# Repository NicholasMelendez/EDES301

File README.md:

# EDES301
Repository for EDES301 course work

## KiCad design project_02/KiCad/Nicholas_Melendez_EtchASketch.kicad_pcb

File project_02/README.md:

# EDES301 Project_02: EtchASketch PCB Design

For my Second project in EDES301, I decided to design an Etch A Sketch PCB using KiCad. I was responsible for the KiCad Symbol and Footprint libraries, the KiCad Schematic, and the KiCad PCB layout. 

The EtchASketch was designed using the PocketBeagle Microprocessor, and it contains the following components:

* One Adafruit 2.8" TFT LCD with Touchscreen Breakout Board w/MicroSD Socket ( to Display EtchASketch Art)

* Two potentiometers ( To operate and draw using the EtchASketch)

* Three LEDs (Red, Green, and Blue for user color indication)

* Two Button (To swap colors and to reset the screen)

* One USB port (For future expansion)

* An Image of the GOAT Gojo Satoru

In addition to the KiCad files, the directory for project_02 also contains generated Gerber and Drill files for the PCB, A generated Bill of Materials document, Images of the Top and Bottom views of the PCB, a PDF of the Schematic, and a presentation containing the mechanical block diagram and the system block diagram

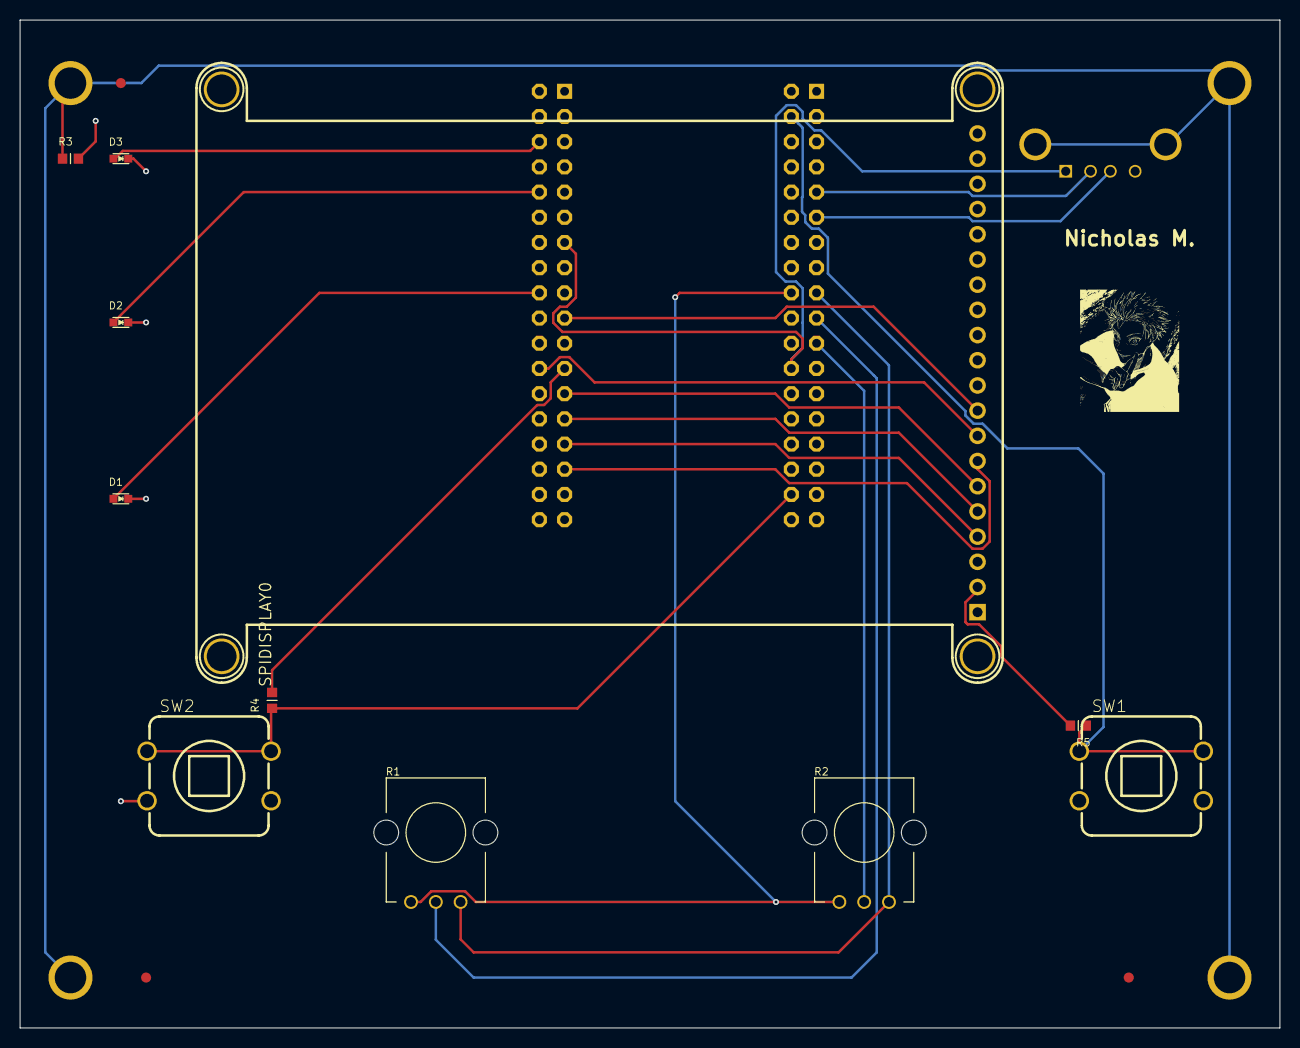
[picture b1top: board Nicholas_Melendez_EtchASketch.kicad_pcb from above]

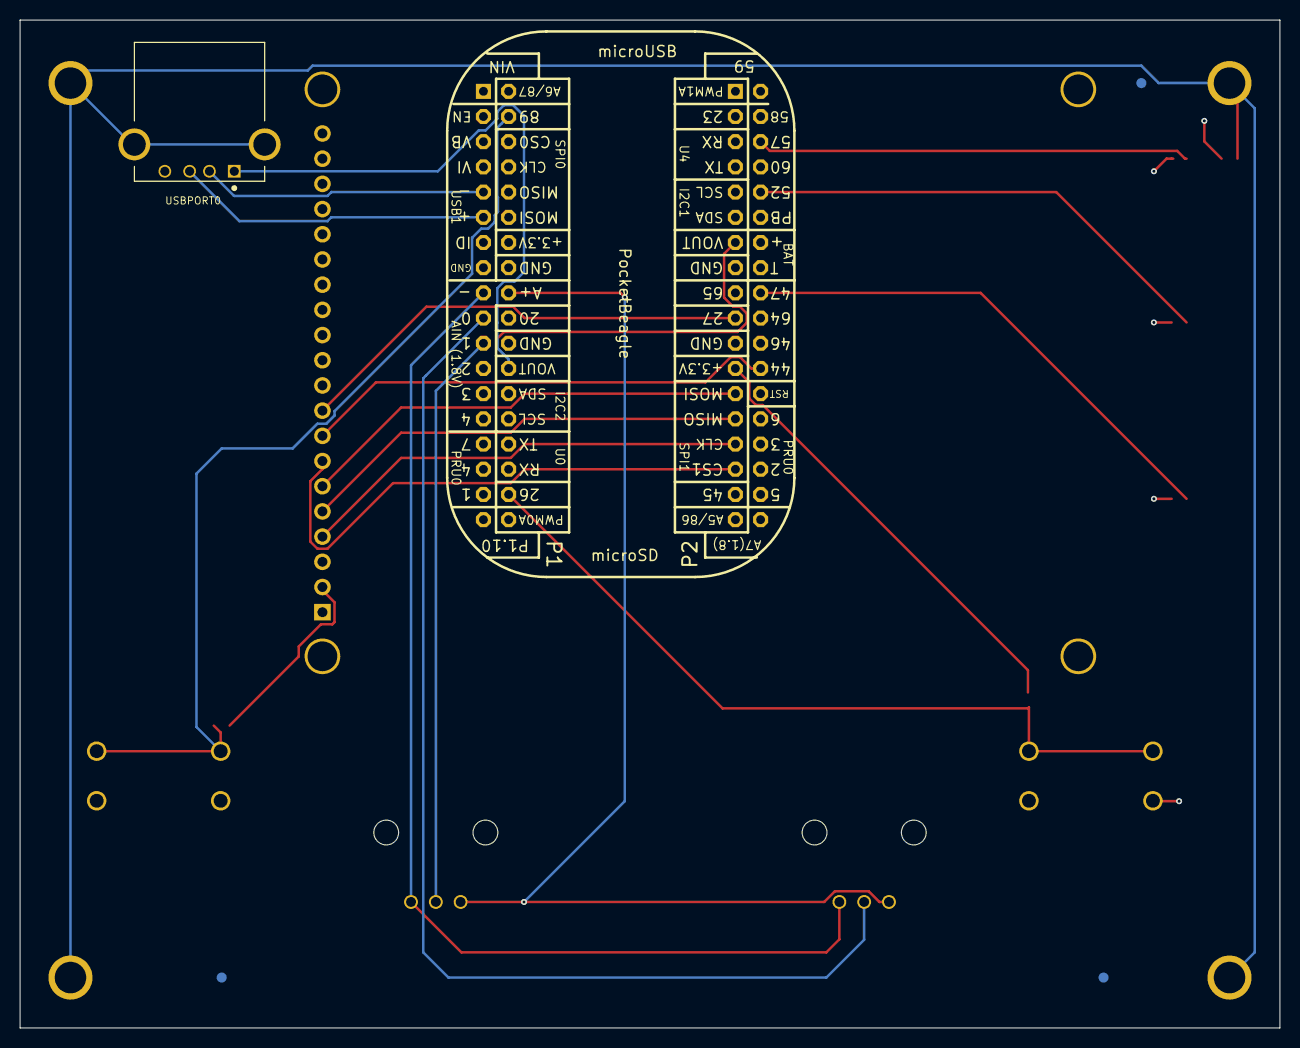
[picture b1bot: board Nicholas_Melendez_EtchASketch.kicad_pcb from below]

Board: 4 copper layers, 127.0 x 101.6 mm, 24 parts (5 on the bottom side), 21 nets.

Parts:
D1: BLUE_LED; EIA-STD
D2: GREEN_LED; EIA-STD
D3: RED_LED; EIA-STD
FUD1, FUD2, FUD3, FUD4, FUD5, FUD6: FIDUCIAL; FIDUCIAL_40MIL
MGT1, MGT2, MGT3, MGT4: MOUNTING_HOLE
Nicholas M.: LOGO; Nicholas_Melendez_GOJO
R1, R2: POTENTIOMETER; POT-PO90S
R3, R4, R5: 1k; R0603
SPIDISPLAY0: SCREEN
SW1, SW2: PUSH_BUTTON; BUTTON_12.5MM
U1: POCKETBEAGLE
USBPORT0: 292303-1; TE_292303-1

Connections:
ANALOG_GND: R1.CW, R2.CW, U1.P1_17
BLUE_LED: D1.ANODE, U1.P2_18
BUTTON_1: R5.1, SW1.1, SW1.3, U1.P1_04
BUTTON_2: R4.1, SW2.1, SW2.3, U1.P1_34
CGND: MGT1.P$1, MGT2.P$1, MGT3.P$1, MGT4.P$1, R3.1, USBPORT0.SH1, USBPORT0.SH2
CLK: SPIDISPLAY0.CLK, U1.P2_29
CS: SPIDISPLAY0.CS, U1.P2_31
DC: SPIDISPLAY0.DC, U1.P2_24
DM: U1.P1_09, USBPORT0.2
DP: U1.P1_11, USBPORT0.3
GND: D1.CATHODE, D2.CATHODE, D3.CATHODE, R3.2, SPIDISPLAY0.GND, SW1.2, SW1.4, SW2.2, SW2.4, U1.P1_15, U1.P1_16, U1.P1_22, U1.P2_15, U1.P2_21, USBPORT0.4
GREEN_LED: D2.ANODE, U1.P2_10
MISO: SPIDISPLAY0.MISO, U1.P2_27
MOSI: SPIDISPLAY0.MOSI, U1.P2_25
POT_1: R1.S, U1.P1_19
POT_2: R2.S, U1.P1_21
RED_LED: D3.ANODE, U1.P2_06
RST: SPIDISPLAY0.RST, U1.P2_19
VDD_1P8V: R1.CCW, R2.CCW, U1.P1_18
VDD_3P3V: R4.2, R5.2, SPIDISPLAY0.VIN, U1.P1_14, U1.P2_23
VDD_5V: U1.P1_24, U1.P2_13, USBPORT0.1

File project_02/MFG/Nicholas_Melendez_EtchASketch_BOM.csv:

"Id";"Designator";"Footprint";"Quantity";"Designation";"Supplier and ref";
1;"D1";"EIA-STD";1;"BLUE_LED";;;
2;"D2";"EIA-STD";1;"GREEN_LED";;;
3;"D3";"EIA-STD";1;"RED_LED";;;
4;"FUD1, FUD2, FUD3, FUD4, FUD5, FUD6";"FIDUCIAL_40MIL";6;"FIDUCIAL";;;
5;"MGT1, MGT2, MGT3, MGT4";"MOUNTING_HOLE";4;"MOUNTING_HOLE";;;
6;"R1, R2";"POT-PO90S";2;"POTENTIOMETER";;;
7;"R3, R4, R5";"R0603";3;"1k";;;
8;"SPIDISPLAY0";"SCREEN";1;"SCREEN";;;
9;"SW1, SW2";"BUTTON_12.5MM";2;"PUSH_BUTTON";;;
10;"U1";"POCKETBEAGLE";1;"POCKETBEAGLE";;;
11;"USBPORT0";"TE_292303-1";1;"292303-1";;;

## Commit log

2026-02-06 Updating README.md
2026-02-24 Added and Updated assignment_03 and python simple calc
2026-02-24 Updated Calculator to Support right shift, left shift, modulo, and exponentation
2026-02-24 Added memory map and its files
2026-02-24 Added Blink Program for PocketBeagle USR3 LED, Blinks USR3 LED at 5 Hz
2026-02-24 Updated simple_calc.py to support python 2 raw input
2026-02-25 Added folder project_01 and project proposal
2026-02-25 Added simple button program
2026-02-25 Add README.md for Epic Audio Analyzer project
2026-02-25 Create Melendez_EDES301_project_01_proposal
2026-02-25 Add README file for EPIC Audio Analyzer project
2026-03-02 Added updated project proposal
    Updated project proposal containing updated power and system block diagrams
2026-03-13 Added Software Diagram for project_01
2026-03-25 updating repository with completed projects
2026-04-16 Updated python files
2026-04-16 updating more python files
2026-04-16 Added README.md for project_01
2026-04-16 Editing README.md
2026-04-16 removing extra files
2026-04-16 Updated REAME.md
2026-04-16 README.md
2026-04-17 Updated software for FFT and Microphone configuration
2026-04-17 Updated Display Software and README.md
2026-04-18 Update README with additional pyaudio installation command
    Added installation command for pyaudio using python3.
2026-04-18 Update README with additional library installation
    Added installation instructions for adafruit-charlcd.
2026-04-21 Complete restore: New directory structure, no submodules
2026-04-21 Created new project_01 to due to corrupted files
2026-04-21 emptied out old directory and added it to new one
2026-04-21 Updated new README
2026-04-21 updating readme
2026-04-24 Updating Software
2026-04-26 Update software for project_01 to fix bugs
2026-04-26 Updated microphone sensitivity
2026-04-28 Updated software and README
2026-05-01 Update README with LCD update rate information
    Added note about LCD update rate in README.
2026-05-01 Fix formatting in README for clarity
2026-05-04 Create docs
2026-05-04 Create documantation
2026-05-04 Create Hardware
2026-05-04 Add KiCAD directory to project_02
2026-05-04 Create MFG
2026-05-04 Create p
2026-05-05 Rename Nicholas Melendez EtchASketch PDF.pdf to Nicholas Melendez EtchASketch Schmematic PDF.pdf
2026-05-05 Rename Nicholas Melendez EtchASketch Schmematic PDF.pdf to Nicholas Melendez EtchASketch Schematic PDF.pdf
2026-05-05 Update README with project details for Etch A Sketch
    Added project description and details for Etch A Sketch PCB design.
2026-05-05 Fix header formatting in README.md
    Added a space after the '#' in the project title.
2026-05-05 Added new PCB and Library to account for Bitmap Addition
2026-05-05 Readded Gerber and Drill Files
2026-05-05 Add Nicholas Melendez EtchASketch BOM file
2026-05-06 Add image of Gojo Satoru to README
    Added an image of Gojo Satoru to the README.
2026-05-06 Fix typo in README for PCB Design
